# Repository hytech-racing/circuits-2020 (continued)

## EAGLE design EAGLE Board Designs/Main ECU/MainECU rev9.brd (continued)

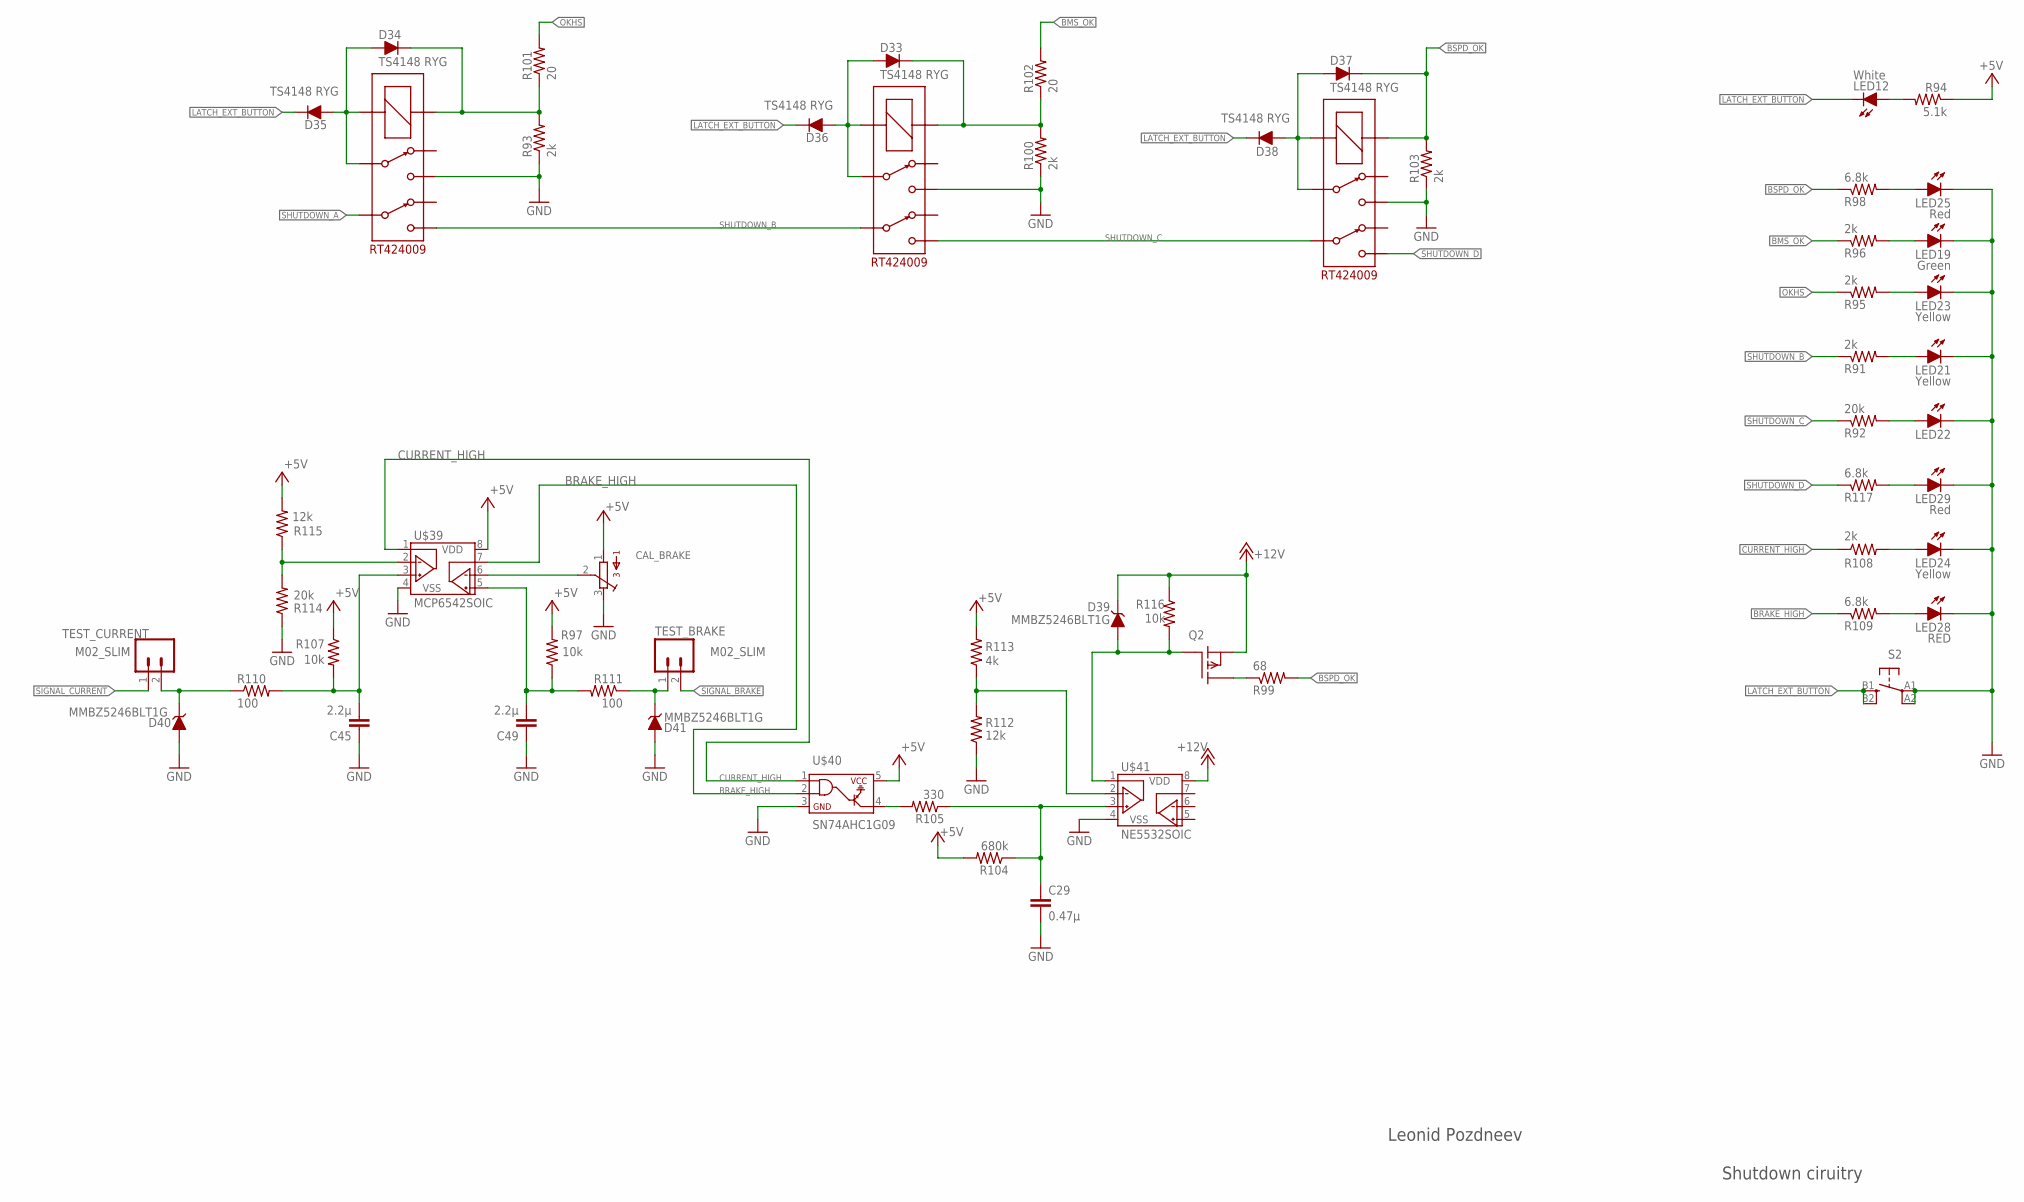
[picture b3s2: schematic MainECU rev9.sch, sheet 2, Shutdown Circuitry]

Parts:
C29: 0.47µ; 0603-CAP
C45, C49: 2.2µ; 0603-CAP
CAL_BRAKE: TRIMPOT_3296C; TRIMPOT_3296
D33, D34, D35, D36, D37, D38: TS4148 RYG; 0805_D
D39, D40, D41: MMBZ5246BLT1G; SOT23
IMD_SHUTDOWN_RLY1: RT424009; RELAY_DPDT
LED12: White; LED-805
LED19, LED22: Green; LED-805
LED21, LED23, LED24: Yellow; LED-805
LED25, LED29: Red; LED-805
LED28: RED; LED-805
Q2: P-CHANNEL_MOSFET_DMP3099L-7; SOT23
R91, R93, R95, R96, R100, R103, R108: 2k; 0603-RES
R92, R114: 20k; 0603-RES
R94: 5.1k; 0603-RES
R97, R107, R116: 10k; 0603-RES
R98, R109, R117: 6.8k; 0603-RES
R99: 68; 0603-RES
R101, R102: 20; 0603-RES
R104: 680k; 0603-RES
R105: 330; 0603-RES
R110, R111: 100; 0603-RES
R112, R115: 12k; 0603-RES
R113: 4k; 0603-RES
S2: BTN_10-XXSMD; TACTILE_SWITCH_SMD_6.2MM_TALL
TEST_BRAKE: M02_SLIM; 1X02_SLIM
TEST_CURRENT: M02_SLIM; 1X02_SLIM
U$37, U$38: RT424009; RELAY_DPDT
U$39: MCP6542SOIC; SOIC-08
U$40: SN74AHC1G09; SOT-23-5
U$41: NE5532SOIC; SOIC-08

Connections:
+5V: CAL_BRAKE.1, R94.1, R97.2, R104.2, R107.1, R113.2, R115.2, U$39.8 (VDD), U$40.5; also elsewhere on the board
+12V: D39.3 (C), Q2.2 (S), R116.1, U$41.8 (VDD); also elsewhere on the board
BMS_OK: R96.1, R102.2; also elsewhere on the board
BMS_PWR_STEP1: D33.A, D36.A, U$38.3, U$38.COIL-
BRAKE_HIGH: R109.1, U$39.7 (VOUTB), U$40.2
BSPD_OK: D37.C, R98.1, R99.2, R103.2, U$37.COIL+; also elsewhere on the board
CURRENT_HIGH: R108.1, U$39.1 (VOUTA), U$40.1
GND: C29.2, C45.1, C49.1, CAL_BRAKE.3, D40.1 (A), D41.1 (A), IMD_SHUTDOWN_RLY1.4, LED19.C, LED21.C, LED22.C, LED23.C, LED24.C, LED25.C, LED28.C, LED29.C, R93.1, R100.1, R103.1, R112.1, R114.1, S2.A1, S2.A2 (P1), U$37.4, U$38.4, U$39.4 (VSS), U$40.3, U$41.4 (VSS); also elsewhere on the board
IMD_PWR_STEP1: D34.A, D35.A, IMD_SHUTDOWN_RLY1.3, IMD_SHUTDOWN_RLY1.COIL-
LATCH_EXT_BUTTON: D35.C, D36.C, D38.C, LED12.C, S2.B1 (S), S2.B2 (S1); also elsewhere on the board
unnamed: Q2.3 (D), R99.1
unnamed: D34.C, IMD_SHUTDOWN_RLY1.COIL+, R93.2, R101.1
unnamed: D33.C, R100.2, R102.1, U$38.COIL+
unnamed: D40.3 (C), R110.1, TEST_CURRENT.2
unnamed: D41.3 (C), R111.1, TEST_BRAKE.1
unnamed: LED21.A, R91.2
unnamed: LED22.A, R92.2
unnamed: LED12.A, R94.2
unnamed: LED23.A, R95.2
unnamed: LED19.A, R96.2
unnamed: LED24.A, R108.2
unnamed: LED28.A, R109.2
unnamed: R114.2, R115.1, U$39.2 (VINA-)
unnamed: D37.A, D38.A, U$37.3, U$37.COIL-
unnamed: C45.2, R107.2, R110.2, U$39.3 (VINA+)
unnamed: R105.2, U$40.4
unnamed: LED25.A, R98.2
unnamed: C29.1, R104.1, R105.1, U$41.3 (VINA+)
unnamed: R112.2, R113.1, U$41.2 (VINA-)
unnamed: CAL_BRAKE.2, U$39.6 (VINB-)
unnamed: D39.1 (A), Q2.1 (G), R116.2, U$41.1 (VOUTA)
unnamed: LED29.A, R117.2
OKHS: R95.1, R101.2; also elsewhere on the board
SHUTDOWN_A: IMD_SHUTDOWN_RLY1.6; also elsewhere on the board
SHUTDOWN_B: IMD_SHUTDOWN_RLY1.5, R91.1, U$38.6; also elsewhere on the board
SHUTDOWN_C: R92.1, U$37.6, U$38.5; also elsewhere on the board
SHUTDOWN_D: R117.1, U$37.5; also elsewhere on the board
SIGNAL_BRAKE: TEST_BRAKE.2; also elsewhere on the board
SIGNAL_BRAKE_FILT1: C49.2, R97.1, R111.2, U$39.5 (VINB+)
SIGNAL_CURRENT: TEST_CURRENT.1; also elsewhere on the board

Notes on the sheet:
Leonid Pozdneev
Shutdown ciruitry

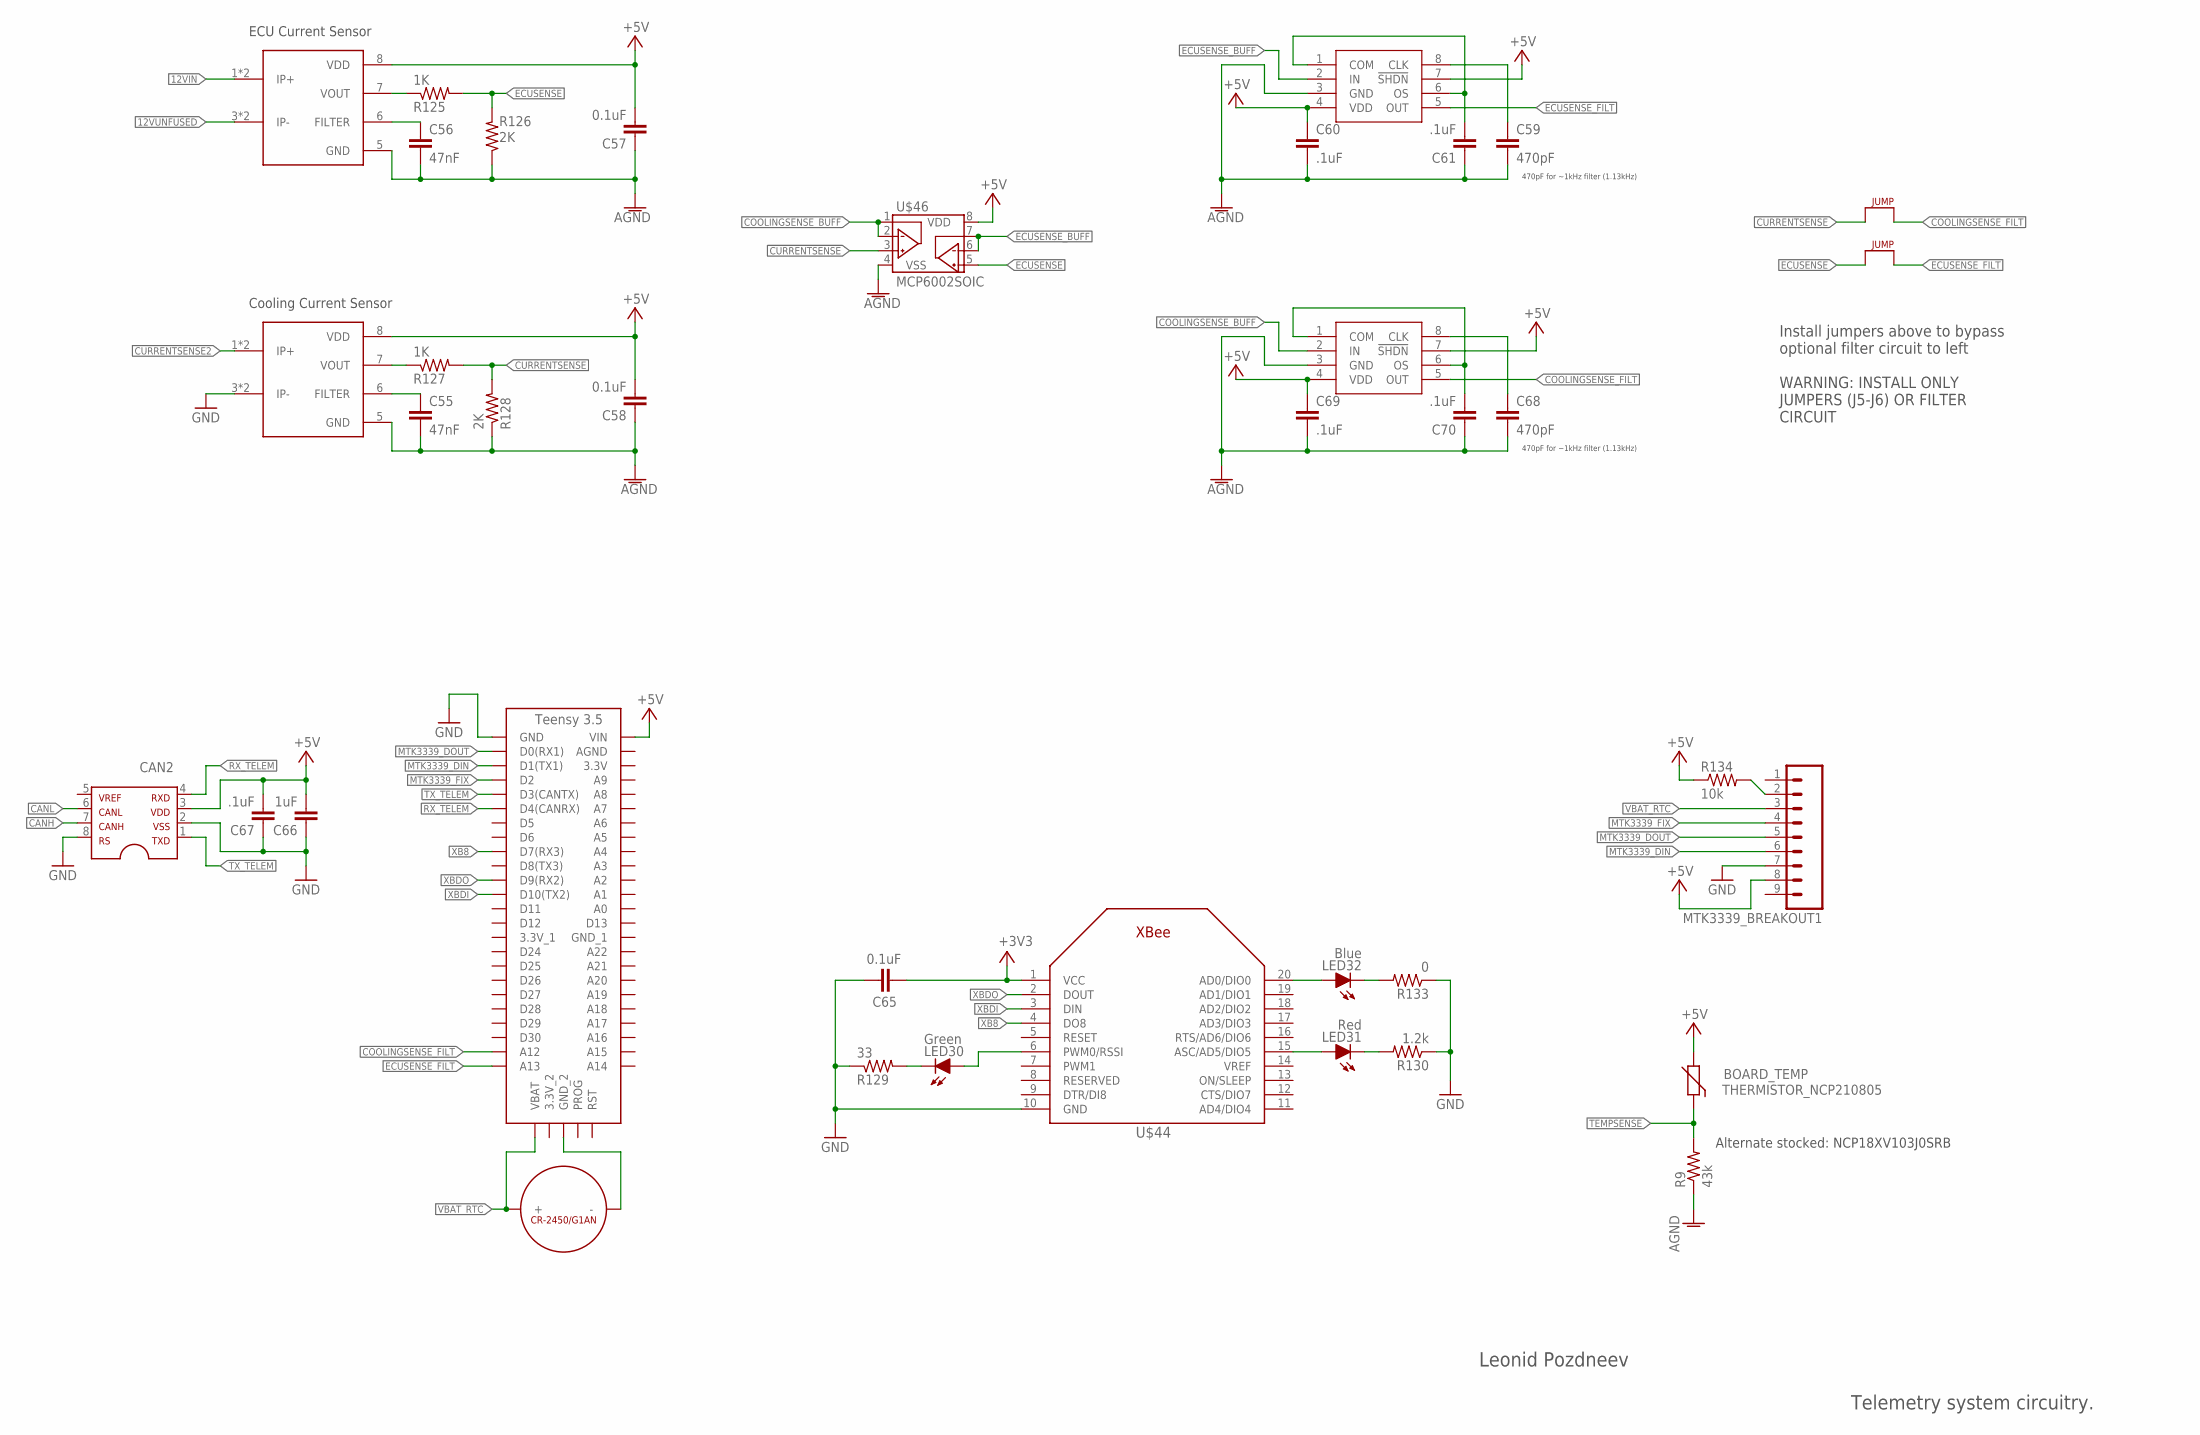
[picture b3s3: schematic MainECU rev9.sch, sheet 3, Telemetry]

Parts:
BOARD_TEMP: THERMISTOR_NCP210805; 0805
C55, C56: 47nF; 0603-CAP
C57, C58, C65: 0.1uF; 0603-CAP
C59, C68: 470pF; 0603-CAP
C60, C61, C67, C69, C70: .1uF; 0603-CAP
C66: 1uF; 0603-CAP
CAN2: MCP2551; SOIC-08
J15, J16: JUMPER; 0805
LED30: Green; LED-805
LED31: Red; LED-805
LED32: Blue; LED-805
MTK3339_BREAKOUT1: M09; 1X09
R9: 43k; 0603-RES
R125, R127: 1K; 0603-RES
R126, R128: 2K; 0603-RES
R129: 33; 0603-RES
R130: 1.2k; 0603-RES
R133: 0; 0603-RES
R134: 10k; 0603-RES
U$43: TEENSY_3.5_EXT
U$44: XBEE
U$45: CR-2450/G1AN
U$46: MCP6002SOIC; SOIC-08
U$47, U$51: MAX7480; SOIC-08
U$49, U$50: ACHS-7121; SOP8

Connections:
12VIN: U$49.1 (IP+), U$49.2 (IP+); also elsewhere on the board
12VUNFUSED: U$49.3 (IP-), U$49.4 (IP-); also elsewhere on the board
+3V3: C65.1, U$44.1 (VCC); also elsewhere on the board
+5V: BOARD_TEMP.1, C57.2, C58.2, C60.1, C66.2, C67.2, C69.1, CAN2.3, MTK3339_BREAKOUT1.8, R134.1, U$43.VIN, U$46.8 (VDD), U$47.4 (VDD), U$47.7 (!SHDN), U$49.8 (VDD), U$50.8 (VDD), U$51.4 (VDD), U$51.7 (!SHDN); also elsewhere on the board
AGND: C55.2, C56.2, C57.1, C58.1, C59.2, C60.2, C61.1, C68.2, C69.2, C70.1, R9.1, R126.1, R128.1, U$46.4 (VSS), U$47.3 (GND), U$49.5 (GND), U$50.5 (GND), U$51.3 (GND); also elsewhere on the board
CANH: CAN2.7; also elsewhere on the board
CANL: CAN2.6; also elsewhere on the board
COOLINGSENSE_BUFF: U$46.1 (VOUTA), U$46.2 (VINA-), U$51.2 (IN)
COOLINGSENSE_FILT: J15.1, U$43.A12, U$51.5 (OUT)
CURRENTSENSE: J15.2, R127.2, R128.2, U$46.3 (VINA+)
CURRENTSENSE2: U$50.1 (IP+), U$50.2 (IP+); also elsewhere on the board
ECUSENSE: J16.2, R125.2, R126.2, U$46.5 (VINB+)
ECUSENSE_BUFF: U$46.6 (VINB-), U$46.7 (VOUTB), U$47.2 (IN)
ECUSENSE_FILT: J16.1, U$43.A13, U$47.5 (OUT)
GND: C65.2, C66.1, C67.1, CAN2.2, CAN2.8, MTK3339_BREAKOUT1.7, R129.1, R130.1, R133.1, U$43.GND, U$44.10 (GND), U$50.3 (IP-), U$50.4 (IP-); also elsewhere on the board
MTK3339_DIN: MTK3339_BREAKOUT1.6, U$43.D1(TX1)
MTK3339_DOUT: MTK3339_BREAKOUT1.5, U$43.D0(RX1)
MTK3339_FIX: MTK3339_BREAKOUT1.4, U$43.D2
unnamed: C55.1, U$50.6 (FILTER)
unnamed: C56.1, U$49.6 (FILTER)
unnamed: LED30.C, R129.2
unnamed: LED30.A, U$44.6 (PWM0/RSSI)
unnamed: LED31.A, U$44.15 (ASC/AD5/DIO5)
unnamed: LED31.C, R130.2
unnamed: LED32.C, R133.2
unnamed: LED32.A, U$44.20 (AD0/DIO0)
unnamed: U$43.GND_2, U$45.-
unnamed: C68.1, U$51.8 (CLK)
unnamed: C59.1, U$47.8 (CLK)
unnamed: MTK3339_BREAKOUT1.2, R134.2
unnamed: R125.1, U$49.7 (VOUT)
unnamed: R127.1, U$50.7 (VOUT)
unnamed: C61.2, U$47.1 (COM), U$47.6 (OS)
unnamed: C70.2, U$51.1 (COM), U$51.6 (OS)
RX_TELEM: CAN2.4, U$43.D4(CANRX)
TEMPSENSE: BOARD_TEMP.2, R9.2; also elsewhere on the board
TX_TELEM: CAN2.1, U$43.D3(CANTX)
VBAT_RTC: MTK3339_BREAKOUT1.3, U$43.VBAT, U$45.+_0 (+), U$45.+_1 (+)
XB8: U$43.D7(RX3), U$44.4 (DO8)
XBDI: U$43.D10(TX2), U$44.3 (DIN)
XBDO: U$43.D9(RX2), U$44.2 (DOUT)

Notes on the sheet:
ECU Current Sensor
Cooling Current Sensor
470pF for ~1kHz filter (1.13kHz)
Install jumpers above to bypass optional filter circuit to left WARNING: INSTALL ONLY JUMPERS (J5-J6) OR FILTER CIRCUIT
Alternate stocked: NCP18XV103J0SRB
Leonid Pozdneev
Telemetry system circuitry.

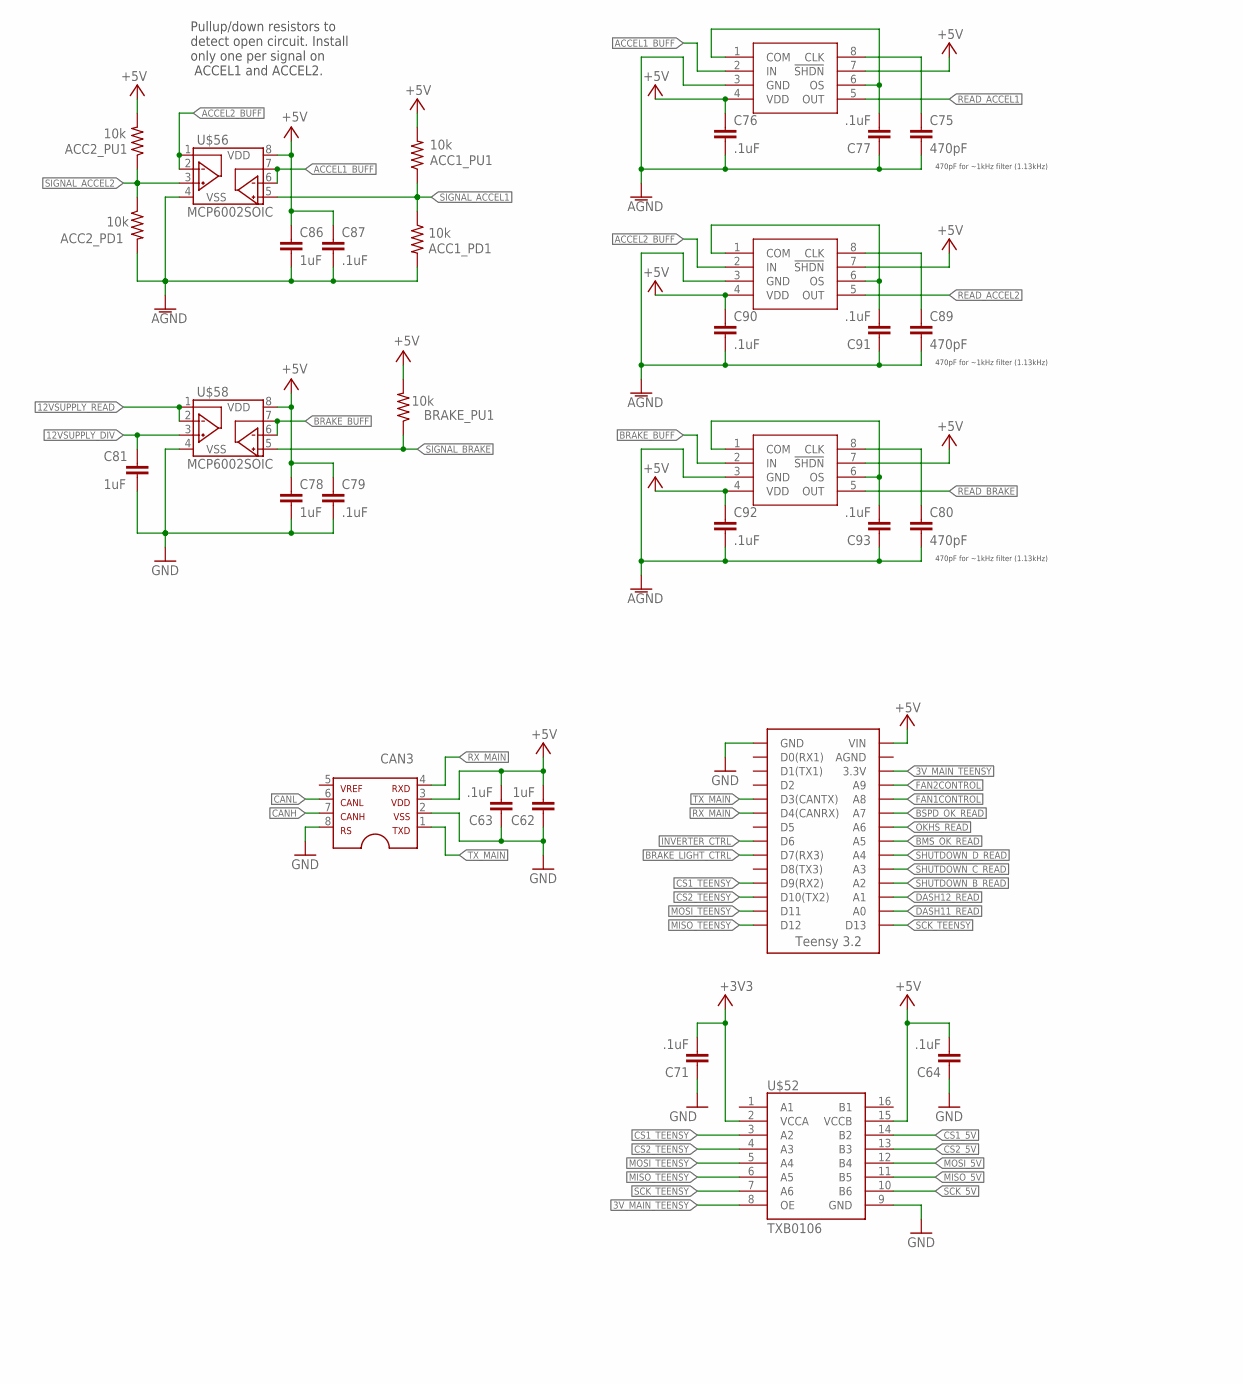
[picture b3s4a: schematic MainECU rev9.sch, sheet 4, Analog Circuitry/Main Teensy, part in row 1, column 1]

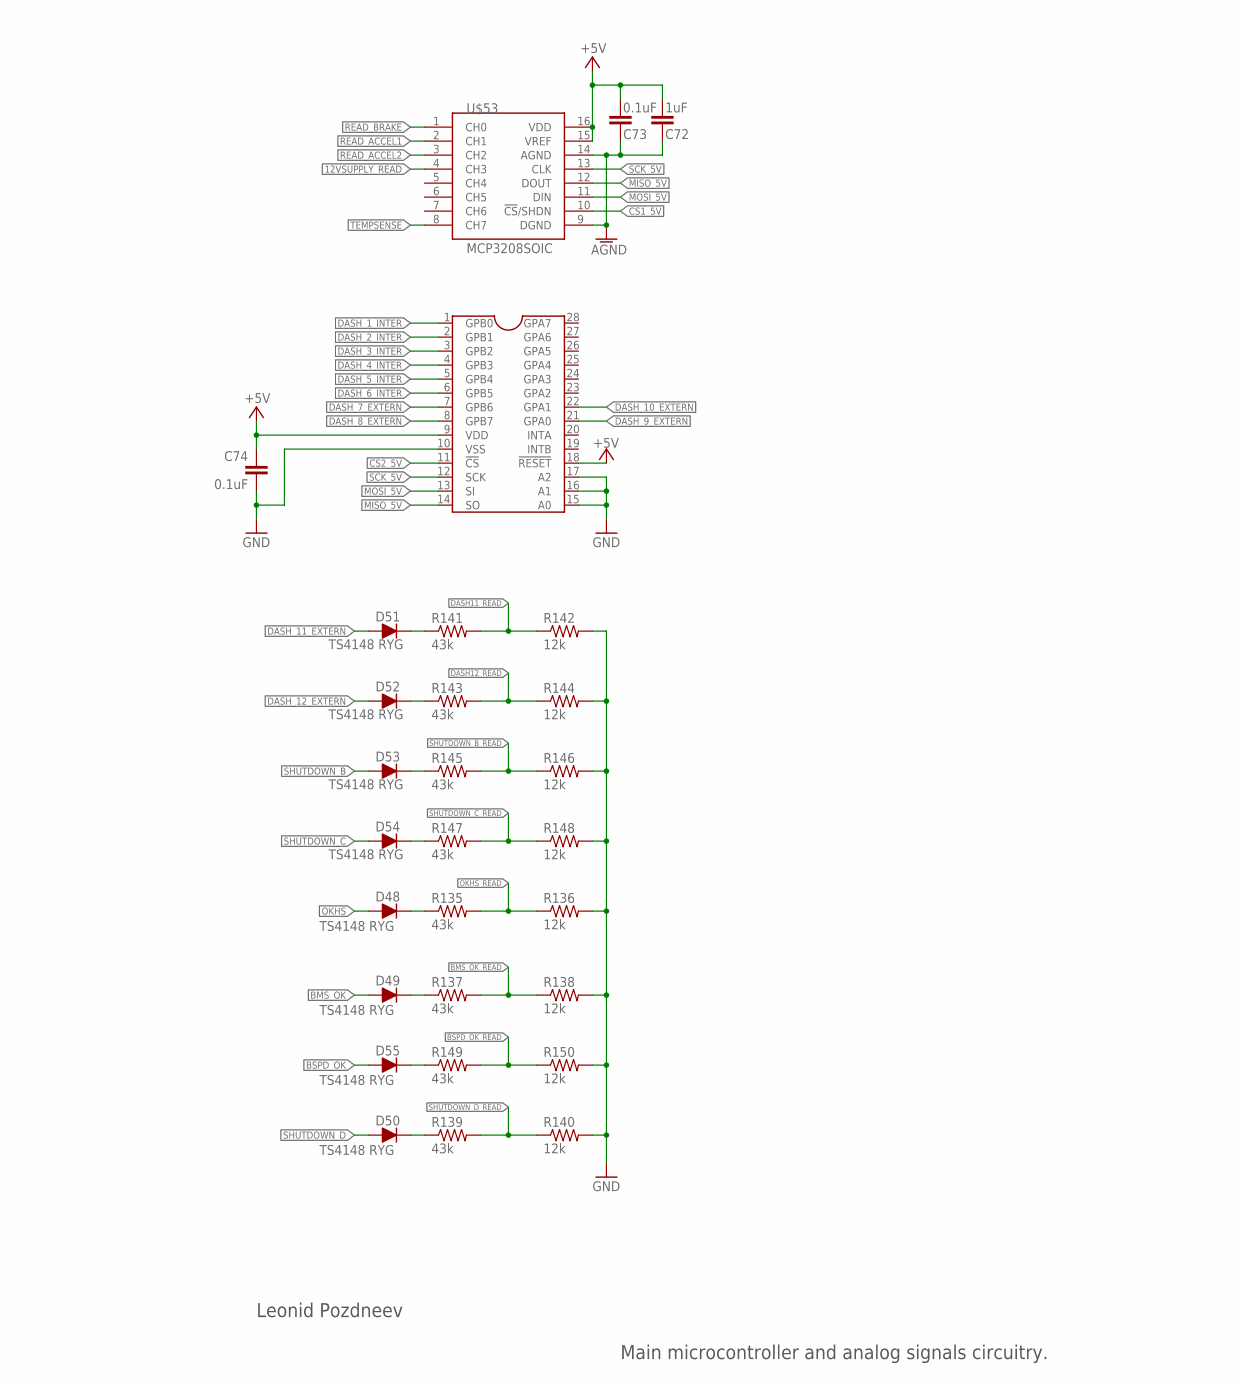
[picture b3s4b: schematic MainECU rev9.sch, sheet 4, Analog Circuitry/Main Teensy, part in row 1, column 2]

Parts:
ACC1_PD1, ACC1_PU1, ACC2_PD1, ACC2_PU1: 10k; 0603-RES
BRAKE_PU1: 10k; 0603-RES
C62, C72, C78, C81, C86: 1uF; 0603-CAP
C63, C64, C71, C76, C77, C79, C87, C90, C91, C92, C93: .1uF; 0603-CAP
C73, C74: 0.1uF; 0603-CAP
C75, C80, C89: 470pF; 0603-CAP
CAN3: MCP2551; SOIC-08
D48, D49, D50, D51, D52, D53, D54, D55: TS4148 RYG; 0805_D
R135, R137, R139, R141, R143, R145, R147, R149: 43k; 0603-RES
R136, R138, R140, R142, R144, R146, R148, R150: 12k; 0603-RES
U$48: TEENSY_3.2_SIMPLE
U$52: TXB0106; TSSOP-16
U$53: MCP3208SOIC; SOIC-16
U$54: MCP23S17SSOP28; SSOP28
U$56, U$58: MCP6002SOIC; SOIC-08
U$57, U$60, U$61: MAX7480; SOIC-08

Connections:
3V_MAIN_TEENSY: U$48.3.3V, U$52.8 (OE)
12VSUPPLY_DIV: C81.1, U$58.3 (VINA+); also elsewhere on the board
12VSUPPLY_READ: U$53.4 (CH3), U$58.1 (VOUTA), U$58.2 (VINA-)
+3V3: C71.2, U$52.2 (VCCA); also elsewhere on the board
+5V: ACC1_PU1.2, ACC2_PU1.2, BRAKE_PU1.2, C62.2, C63.2, C64.2, C72.2, C73.2, C74.1, C76.1, C78.1, C79.1, C86.1, C87.1, C90.1, C92.1, CAN3.3, U$48.VIN, U$52.15 (VCCB), U$53.15 (VREF), U$53.16 (VDD), U$54.9 (VDD), U$54.18 (!RESET), U$56.8 (VDD), U$57.4 (VDD), U$57.7 (!SHDN), U$58.8 (VDD), U$60.4 (VDD), U$60.7 (!SHDN), U$61.4 (VDD), U$61.7 (!SHDN); also elsewhere on the board
ACCEL1_BUFF: U$56.6 (VINB-), U$56.7 (VOUTB), U$57.2 (IN)
ACCEL2_BUFF: U$56.1 (VOUTA), U$56.2 (VINA-), U$60.2 (IN)
AGND: ACC1_PD1.2, ACC2_PD1.2, C72.1, C73.1, C75.2, C76.2, C77.1, C80.2, C86.2, C87.2, C89.2, C90.2, C91.1, C92.2, C93.1, U$53.9 (DGND), U$53.14 (AGND), U$56.4 (VSS), U$57.3 (GND), U$60.3 (GND), U$61.3 (GND); also elsewhere on the board
BMS_OK: D49.A; also elsewhere on the board
BMS_OK_READ: R137.2, R138.1, U$48.A5
BRAKE_BUFF: U$58.6 (VINB-), U$58.7 (VOUTB), U$61.2 (IN)
BRAKE_LIGHT_CTRL: U$48.D7(RX3); also elsewhere on the board
BSPD_OK: D55.A; also elsewhere on the board
BSPD_OK_READ: R149.2, R150.1, U$48.A7
CANH: CAN3.7; also elsewhere on the board
CANL: CAN3.6; also elsewhere on the board
CS1_5V: U$52.14 (B2), U$53.10 (!CS!/SHDN)
CS1_TEENSY: U$48.D9(RX2), U$52.3 (A2)
CS2_5V: U$52.13 (B3), U$54.11 (!CS)
CS2_TEENSY: U$48.D10(TX2), U$52.4 (A3)
DASH11_READ: R141.2, R142.1, U$48.A0
DASH12_READ: R143.2, R144.1, U$48.A1
DASH_1_INTER: U$54.1 (GPB0); also elsewhere on the board
DASH_2_INTER: U$54.2 (GPB1); also elsewhere on the board
DASH_3_INTER: U$54.3 (GPB2); also elsewhere on the board
DASH_4_INTER: U$54.4 (GPB3); also elsewhere on the board
DASH_5_INTER: U$54.5 (GPB4); also elsewhere on the board
DASH_6_INTER: U$54.6 (GPB5); also elsewhere on the board
DASH_7_EXTERN: U$54.7 (GPB6); also elsewhere on the board
DASH_8_EXTERN: U$54.8 (GPB7); also elsewhere on the board
DASH_9_EXTERN: U$54.21 (GPA0); also elsewhere on the board
DASH_10_EXTERN: U$54.22 (GPA1); also elsewhere on the board
DASH_11_EXTERN: D51.A; also elsewhere on the board
DASH_12_EXTERN: D52.A; also elsewhere on the board
FAN1CONTROL: U$48.A8; also elsewhere on the board
FAN2CONTROL: U$48.A9; also elsewhere on the board
GND: C62.1, C63.1, C64.1, C71.1, C74.2, C78.2, C79.2, C81.2, CAN3.2, CAN3.8, R136.2, R138.2, R140.2, R142.2, R144.2, R146.2, R148.2, R150.2, U$48.GND, U$52.9 (GND), U$54.10 (VSS), U$54.15 (A0), U$54.16 (A1), U$54.17 (A2), U$58.4 (VSS); also elsewhere on the board
INVERTER_CTRL: U$48.D6; also elsewhere on the board
MISO_5V: U$52.11 (B5), U$53.12 (DOUT), U$54.14 (SO)
MISO_TEENSY: U$48.D12, U$52.6 (A5)
MOSI_5V: U$52.12 (B4), U$53.11 (DIN), U$54.13 (SI)
MOSI_TEENSY: U$48.D11, U$52.5 (A4)
unnamed: D48.C, R135.1
unnamed: D49.C, R137.1
unnamed: D50.C, R139.1
unnamed: D51.C, R141.1
unnamed: D52.C, R143.1
unnamed: D53.C, R145.1
unnamed: D54.C, R147.1
unnamed: D55.C, R149.1
unnamed: C75.1, U$57.8 (CLK)
unnamed: C89.1, U$60.8 (CLK)
unnamed: C77.2, U$57.1 (COM), U$57.6 (OS)
unnamed: C80.1, U$61.8 (CLK)
unnamed: C93.2, U$61.1 (COM), U$61.6 (OS)
unnamed: C91.2, U$60.1 (COM), U$60.6 (OS)
OKHS: D48.A; also elsewhere on the board
OKHS_READ: R135.2, R136.1, U$48.A6
READ_ACCEL1: U$53.2 (CH1), U$57.5 (OUT)
READ_ACCEL2: U$53.3 (CH2), U$60.5 (OUT)
READ_BRAKE: U$53.1 (CH0), U$61.5 (OUT)
RX_MAIN: CAN3.4, U$48.D4(CANRX)
SCK_5V: U$52.10 (B6), U$53.13 (CLK), U$54.12 (SCK)
SCK_TEENSY: U$48.D13, U$52.7 (A6)
SHUTDOWN_B: D53.A; also elsewhere on the board
SHUTDOWN_B_READ: R145.2, R146.1, U$48.A2
SHUTDOWN_C: D54.A; also elsewhere on the board
SHUTDOWN_C_READ: R147.2, R148.1, U$48.A3
SHUTDOWN_D: D50.A; also elsewhere on the board
SHUTDOWN_D_READ: R139.2, R140.1, U$48.A4
SIGNAL_ACCEL1: ACC1_PD1.1, ACC1_PU1.1, U$56.5 (VINB+); also elsewhere on the board
SIGNAL_ACCEL2: ACC2_PD1.1, ACC2_PU1.1, U$56.3 (VINA+); also elsewhere on the board
SIGNAL_BRAKE: BRAKE_PU1.1, U$58.5 (VINB+); also elsewhere on the board
TEMPSENSE: U$53.8 (CH7); also elsewhere on the board
TX_MAIN: CAN3.1, U$48.D3(CANTX)

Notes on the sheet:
Pullup/down resistors to detect open circuit. Install only one per signal on ACCEL1 and ACCEL2.
470pF for ~1kHz filter (1.13kHz)
Leonid Pozdneev
Main microcontroller and analog signals circuitry.

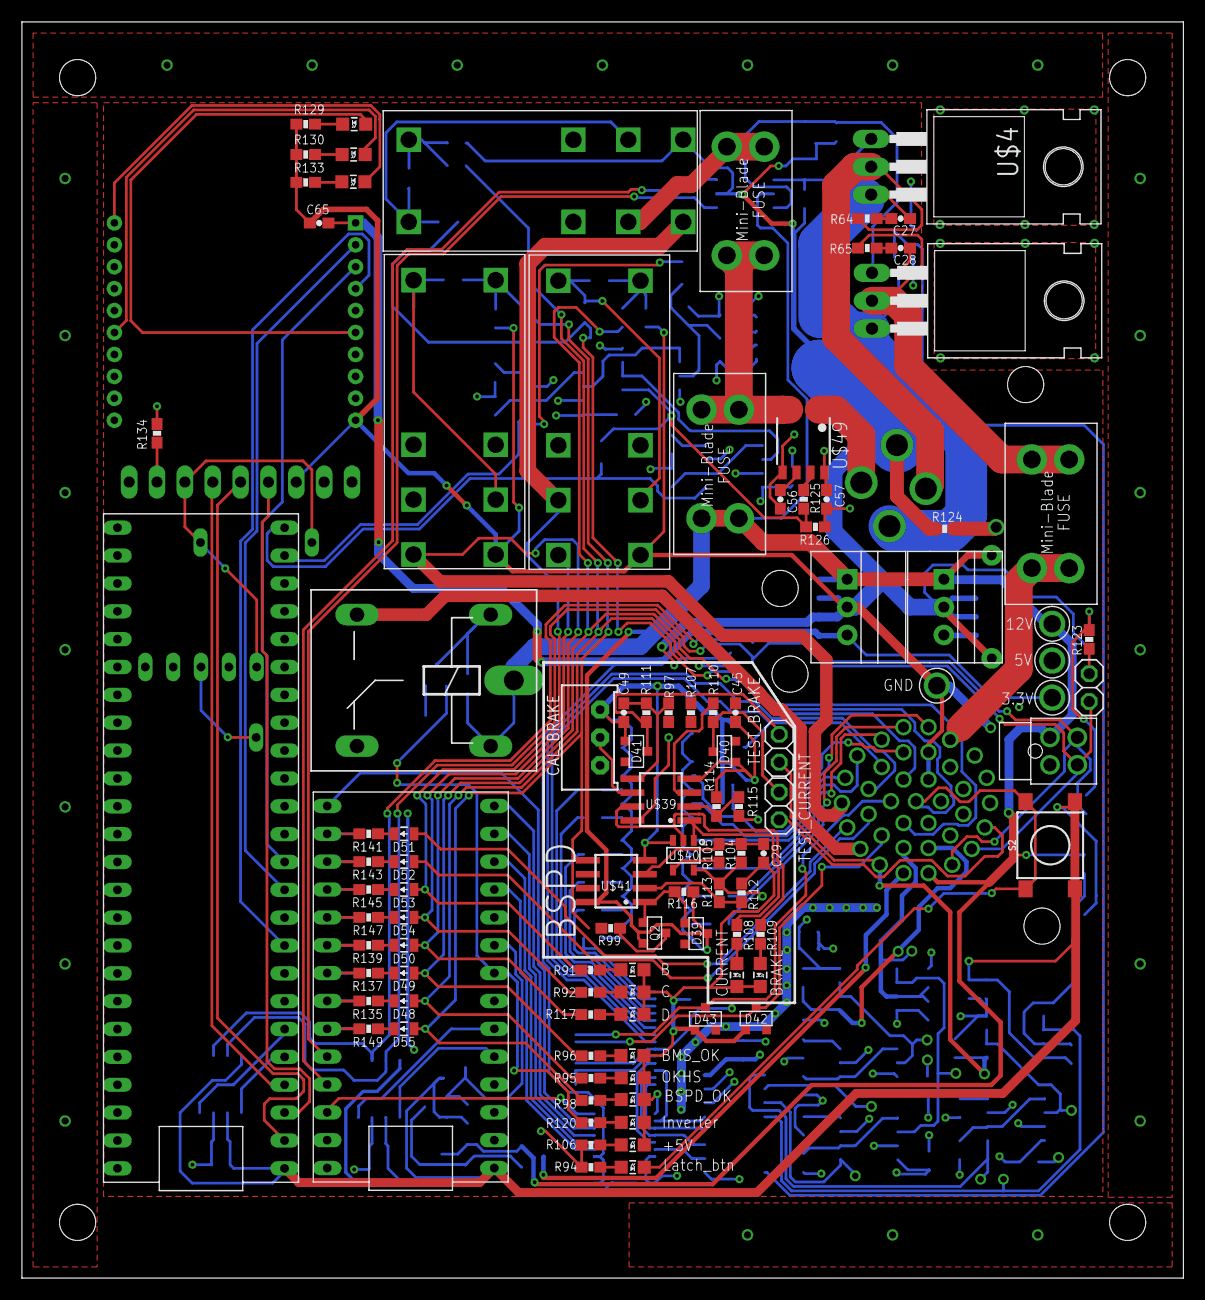
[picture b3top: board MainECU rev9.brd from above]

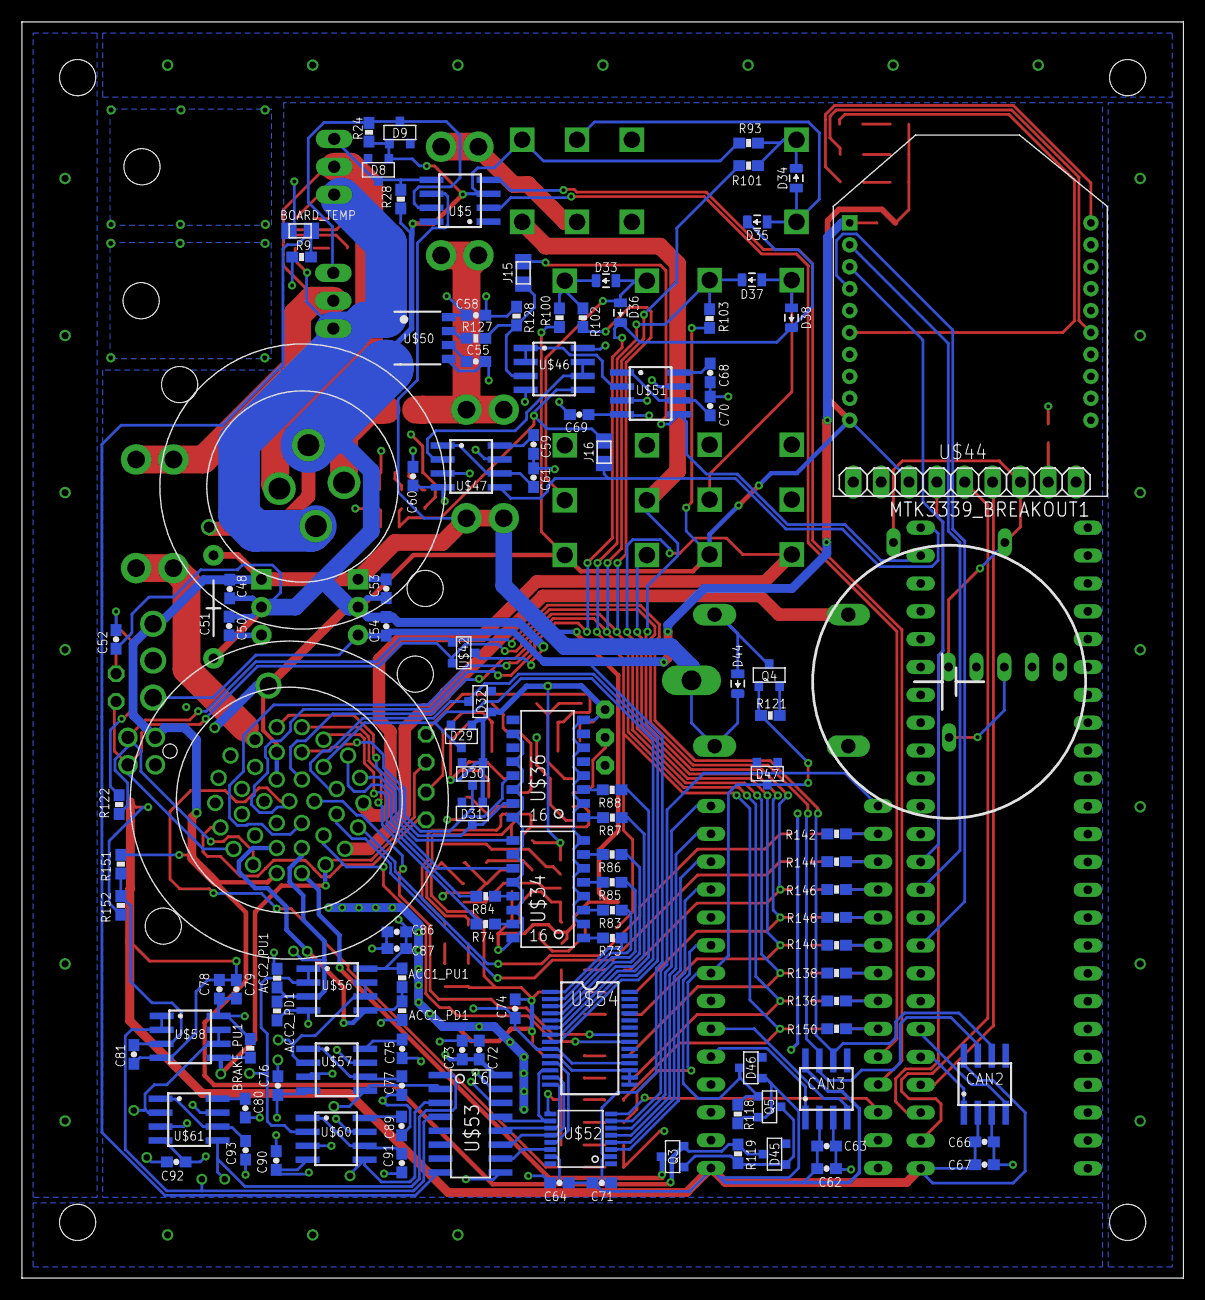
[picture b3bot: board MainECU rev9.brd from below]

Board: 4 copper layers, 105.9 x 114.6 mm, 223 parts (119 on the bottom side), 169 nets.

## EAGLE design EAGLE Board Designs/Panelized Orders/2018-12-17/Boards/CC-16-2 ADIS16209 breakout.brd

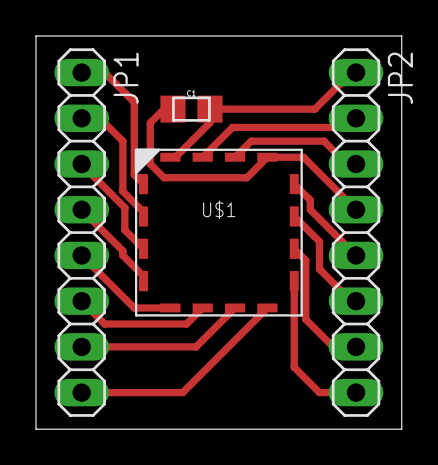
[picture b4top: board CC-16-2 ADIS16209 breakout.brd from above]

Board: 2 copper layers, 20.3 x 21.8 mm, 4 parts (0 on the bottom side), 16 nets.

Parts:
C1: 1µF; 0805
JP1, JP2: 1X08
U$1: ADIS16209; CC-16-2

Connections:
GND: C1.2, JP2.1, U$1.P$16
unnamed: JP1.1, U$1.P$1
unnamed: JP1.2, U$1.P$2
unnamed: JP1.3, U$1.P$3
unnamed: JP1.4, U$1.P$4
unnamed: JP1.5, U$1.P$5
unnamed: JP1.6, U$1.P$6
unnamed: JP1.7, U$1.P$7
unnamed: JP1.8, U$1.P$8
unnamed: JP2.2, U$1.P$15
unnamed: JP2.3, U$1.P$14
unnamed: C1.1, JP2.4, U$1.P$13
unnamed: JP2.5, U$1.P$12
unnamed: JP2.6, U$1.P$11
unnamed: JP2.7, U$1.P$10
unnamed: JP2.8, U$1.P$9
